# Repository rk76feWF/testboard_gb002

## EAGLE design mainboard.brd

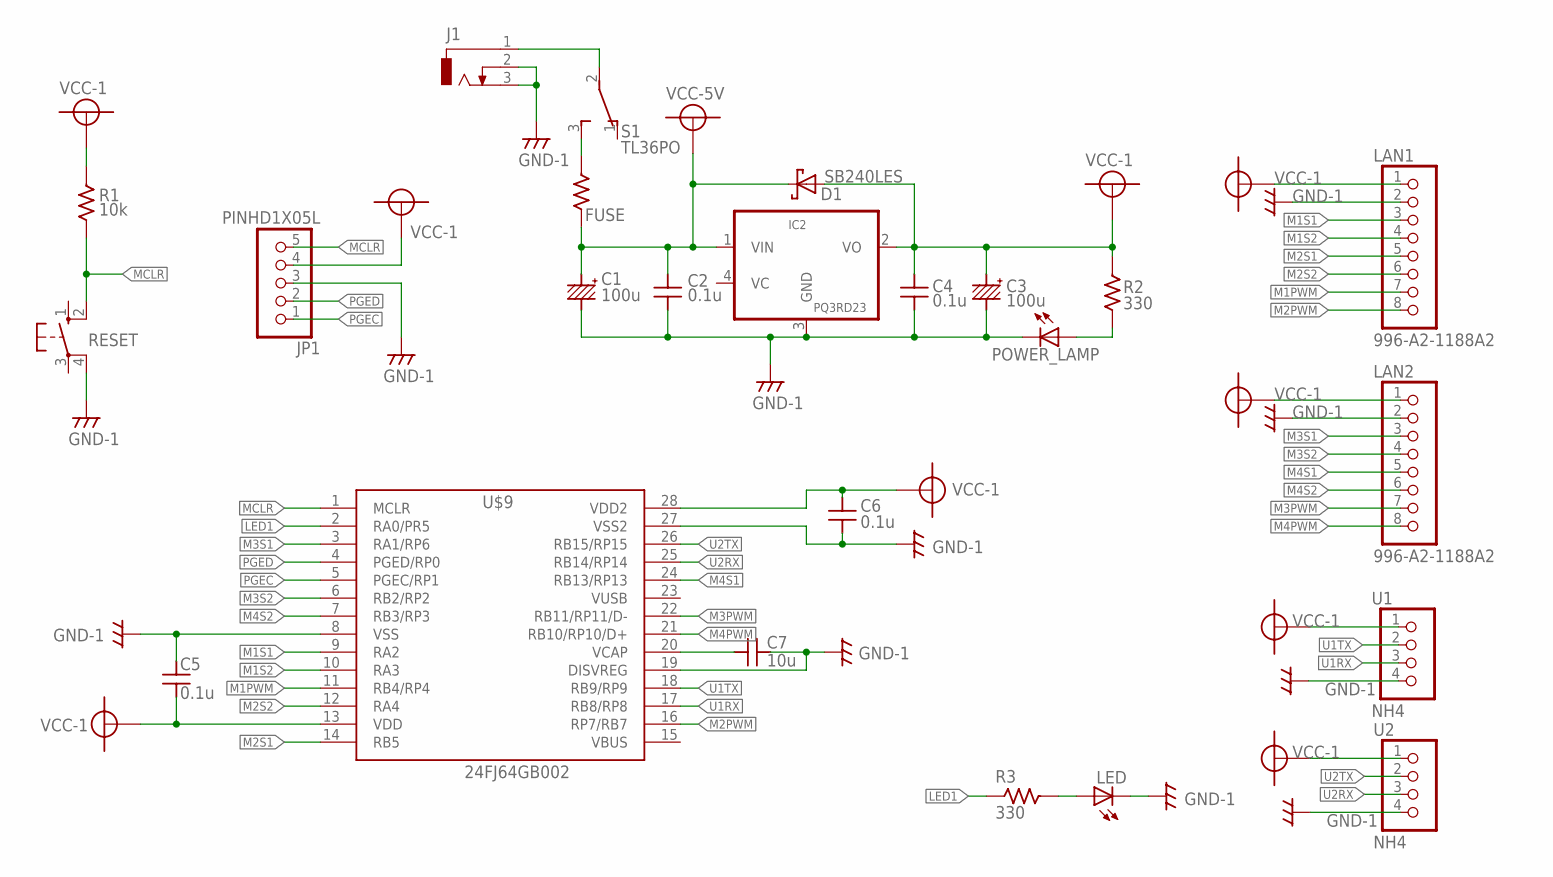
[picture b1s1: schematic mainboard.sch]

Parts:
C1, C3: 100u; CC:3
C2, C4, C5, C6: 0.1u; C:1
C7: 10u; C:1
D1: SB240LES; DO35-7
FUSE: R3216(1206); C3216
IC2: PQ3RD23; TO220BV-4
J1: DCJ0303
JP1: PINHD1X05L; 1X05L
LAN1, LAN2: 996-A2-1188A2
LED: LED""; LED5MM
POWER_LAMP: LED""; LED5MM
R1: 10k; R:1/4W
R2, R3: 330; R:1/4W
RESET: 10-XX; B3F-10XX
S1: TL36PO; TL3XPO
U1, U2: NH4
U$9: 24FJ64GB002; DIL28-3

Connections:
+5V: C1.+ (P$1+), C2.P$1, D1.C, FUSE.1, IC2.1 (VIN)
GND: C1.- (P$2-), C2.P$2, C3.- (P$2-), C4.P$2, C5.P$1, C6.P$2, C7.P$2, IC2.3 (GND), J1.2, J1.3, JP1.3, LAN1.2, LAN2.2, LED.K (C), POWER_LAMP.K (C), RESET.4 (P1), U1.4, U2.4, U$9.8 (VSS), U$9.19 (DISVREG), U$9.27 (VSS2)
LED1: R3.P$1, U$9.2 (RA0/PR5)
M1PWM: LAN1.7, U$9.11 (RB4/RP4)
M1S1: LAN1.3, U$9.9 (RA2)
M1S2: LAN1.4, U$9.10 (RA3)
M2PWM: LAN1.8, U$9.16 (RP7/RB7)
M2S1: LAN1.5, U$9.14 (RB5)
M2S2: LAN1.6, U$9.12 (RA4)
M3PWM: LAN2.7, U$9.22 (RB11/RP11/D-)
M3S1: LAN2.3, U$9.3 (RA1/RP6)
M3S2: LAN2.4, U$9.6 (RB2/RP2)
M4PWM: LAN2.8, U$9.21 (RB10/RP10/D+)
M4S1: LAN2.5, U$9.24 (RB13/RP13)
M4S2: LAN2.6, U$9.7 (RB3/RP3)
MCLR: JP1.5, R1.P$1, RESET.2 (S1), U$9.1 (MCLR)
unnamed: LED.A, R3.P$2
unnamed: J1.1, S1.2
unnamed: POWER_LAMP.A, R2.P$1
unnamed: FUSE.2, S1.3 (S)
unnamed: C7.P$1, U$9.20 (VCAP)
PGEC: JP1.1, U$9.5 (PGEC/RP1)
PGED: JP1.2, U$9.4 (PGED/RP0)
U1RX: U1.3, U$9.17 (RB8/RP8)
U1TX: U1.2, U$9.18 (RB9/RP9)
U2RX: U2.3, U$9.25 (RB14/RP14)
U2TX: U2.2, U$9.26 (RB15/RP15)
VCC-1: C3.+ (P$1+), C4.P$1, C5.P$2, C6.P$1, D1.A, IC2.2 (VO), JP1.4, LAN1.1, LAN2.1, R1.P$2, R2.P$2, U1.1, U2.1, U$9.13 (VDD), U$9.28 (VDD2)

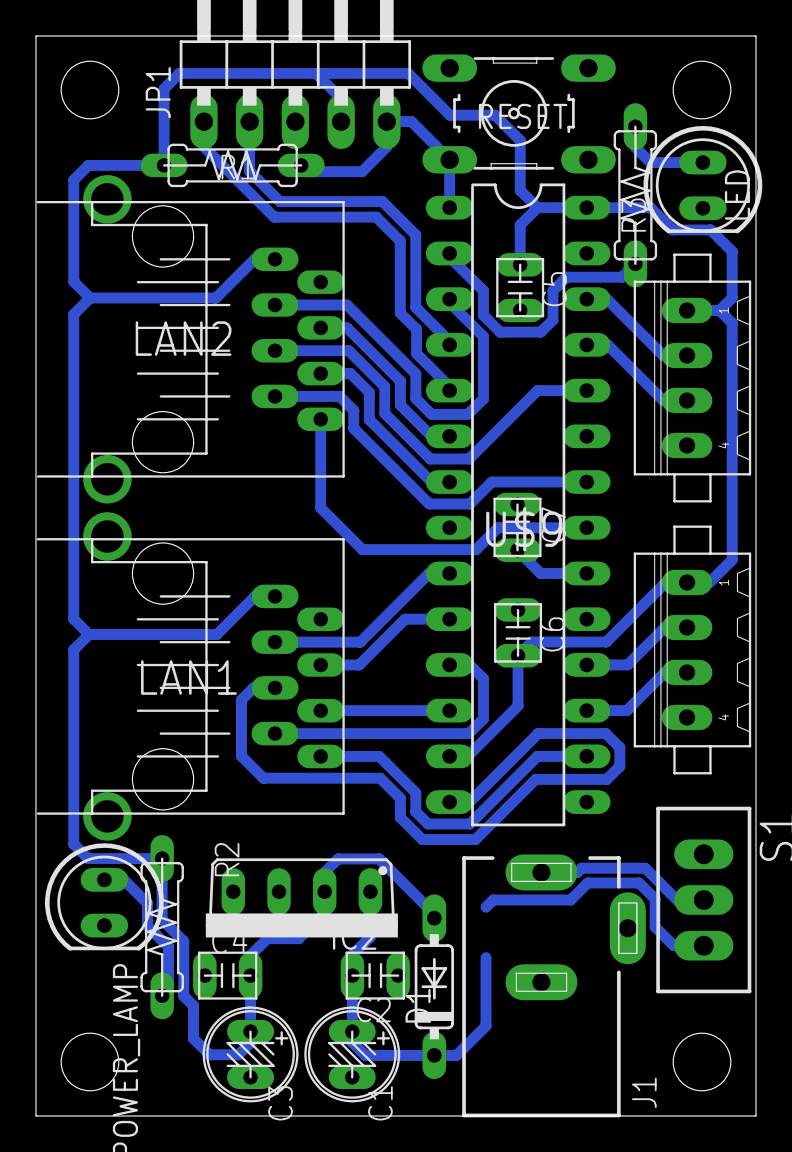
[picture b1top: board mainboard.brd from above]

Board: 2 copper layers, 40.0 x 60.0 mm, 24 parts (1 on the bottom side), 28 nets.

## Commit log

2022-11-18 [Add] 作成したschとbrdを追加
